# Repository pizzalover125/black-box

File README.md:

# black-box
Black Box was a YSWS program ran by @lux in 2025. The premise was simple: 64 LEDs, 5 buttons, and a buzzer. It was a YSWS about limitations. I absolutely LOVED the idea, but never got around to making a Black Box. When fufillment came around, all that was shipped to participants was three breadboards, a bunch of wires, and all the parts to assemble this. I was flabberghasted. All of this money going to breadboards? I knew something had to be done. I made a PCB for #black-box. Read JOURNAL.md for a more detailed story. 

## Images
### Schematic

### PCB

### CAD

## BOM
* 1x Raspberry Pi Pico H ($5.00 from Adafruit) (https://www.adafruit.com/product/5525) 
* 20x 6mm Push Buttons ($2.50 from Adafruit) (https://www.adafruit.com/product/367)
* 1x PS1240 Piezo Buzzer ($1.50 from Adafruit) (https://www.adafruit.com/product/160)
* 1x 1.2" 8x8 LED Matrix ($3.95 from Adafruit) (https://www.adafruit.com/product/455)
**Subtotal: $19.62 (from Adafruit)**
* 1x PCB ($5.30 from JLCPCB)
**Total: 24.92**

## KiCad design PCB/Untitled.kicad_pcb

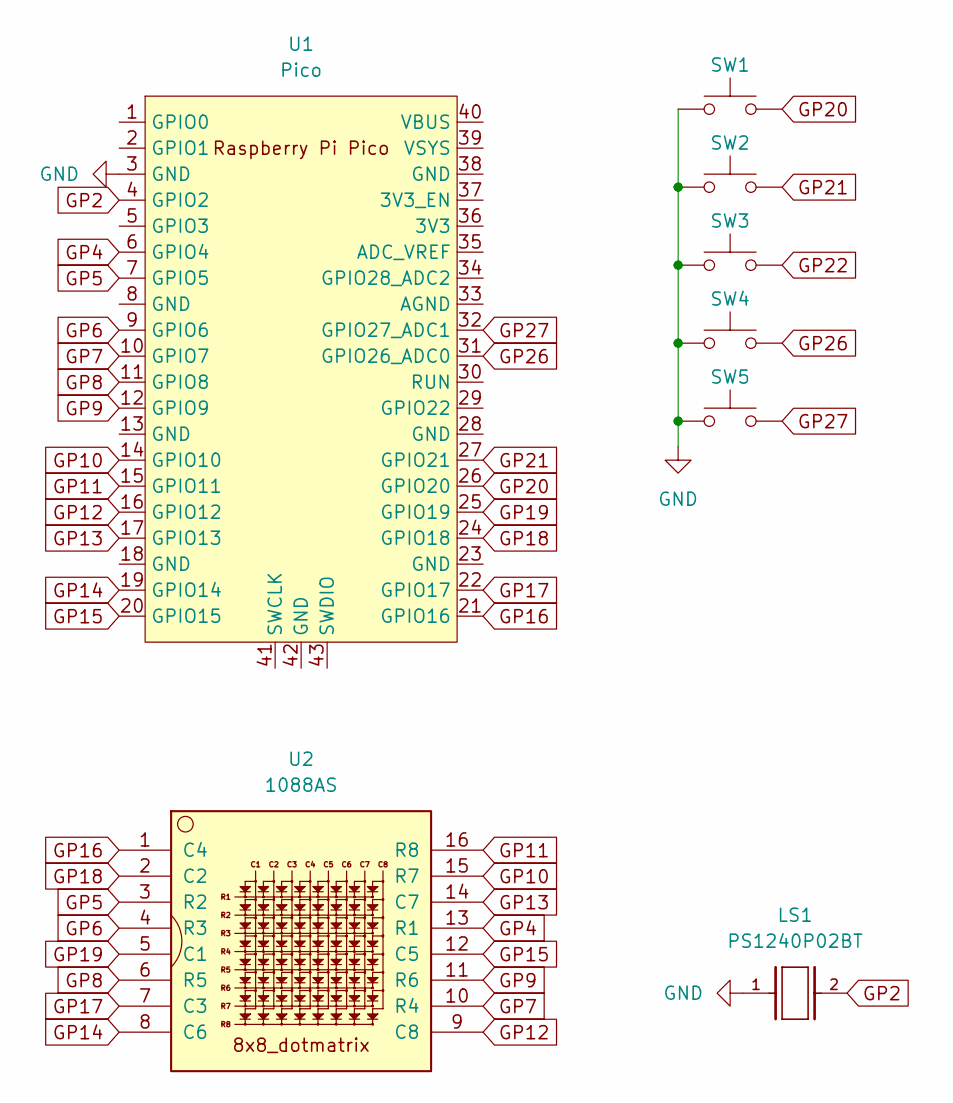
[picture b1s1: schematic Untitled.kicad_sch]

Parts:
LS1: PS1240P02BT; XDCR_PS1240P02BT
SW1, SW2, SW3, SW4, SW5: SW_Push; SW_PUSH_6mm
U1: Pico; RaspberryPi_Pico_Common_THT
U2: 1088AS; LED_1088_Pin_Header

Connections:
GND: LS1.1, SW1.1, SW2.1, SW3.1, SW4.1, SW5.1, U1.3 (GND)
GP2: LS1.2, U1.4 (GPIO2)
GP4: U1.6 (GPIO4), U2.13 (R1)
GP5: U1.7 (GPIO5), U2.3 (R2)
GP6: U1.9 (GPIO6), U2.4 (R3)
GP7: U1.10 (GPIO7), U2.10 (R4)
GP8: U1.11 (GPIO8), U2.6 (R5)
GP9: U1.12 (GPIO9), U2.11 (R6)
GP10: U1.14 (GPIO10), U2.15 (R7)
GP11: U1.15 (GPIO11), U2.16 (R8)
GP12: U1.16 (GPIO12), U2.9 (C8)
GP13: U1.17 (GPIO13), U2.14 (C7)
GP14: U1.19 (GPIO14), U2.8 (C6)
GP15: U1.20 (GPIO15), U2.12 (C5)
GP16: U1.21 (GPIO16), U2.1 (C4)
GP17: U1.22 (GPIO17), U2.7 (C3)
GP18: U1.24 (GPIO18), U2.2 (C2)
GP19: U1.25 (GPIO19), U2.5 (C1)
GP20: SW1.2, U1.26 (GPIO20)
GP21: SW2.2, U1.27 (GPIO21)
GP22: SW3.2
GP26: SW4.2, U1.31 (GPIO26_ADC0)
GP27: SW5.2, U1.32 (GPIO27_ADC1)

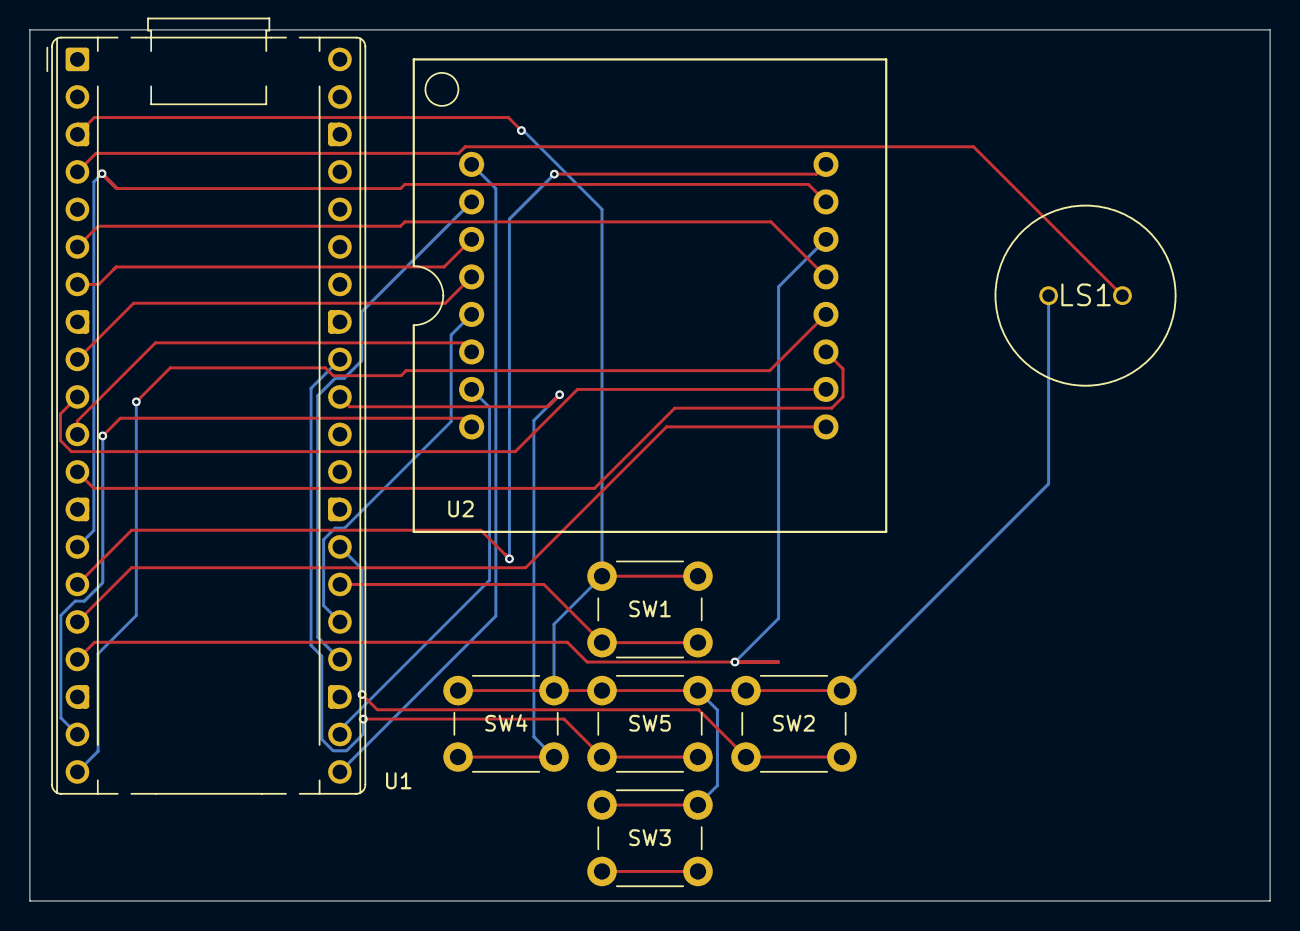
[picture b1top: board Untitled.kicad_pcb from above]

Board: 2 copper layers, 84.0 x 59.0 mm, 8 parts (0 on the bottom side), 22 nets.

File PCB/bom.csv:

Designator,Footprint,Quantity,Value,LCSC Part #
LS1,XDCR_PS1240P02BT,1,PS1240P02BT,
"SW1, SW2, SW3, SW4, SW5",SW_PUSH_6mm,5,SW_Push,
U1,RaspberryPi_Pico_Common_THT,1,Pico,
U2,LED_1088_Pin_Header,1,1088AS,

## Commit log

2025-07-03 Create a
